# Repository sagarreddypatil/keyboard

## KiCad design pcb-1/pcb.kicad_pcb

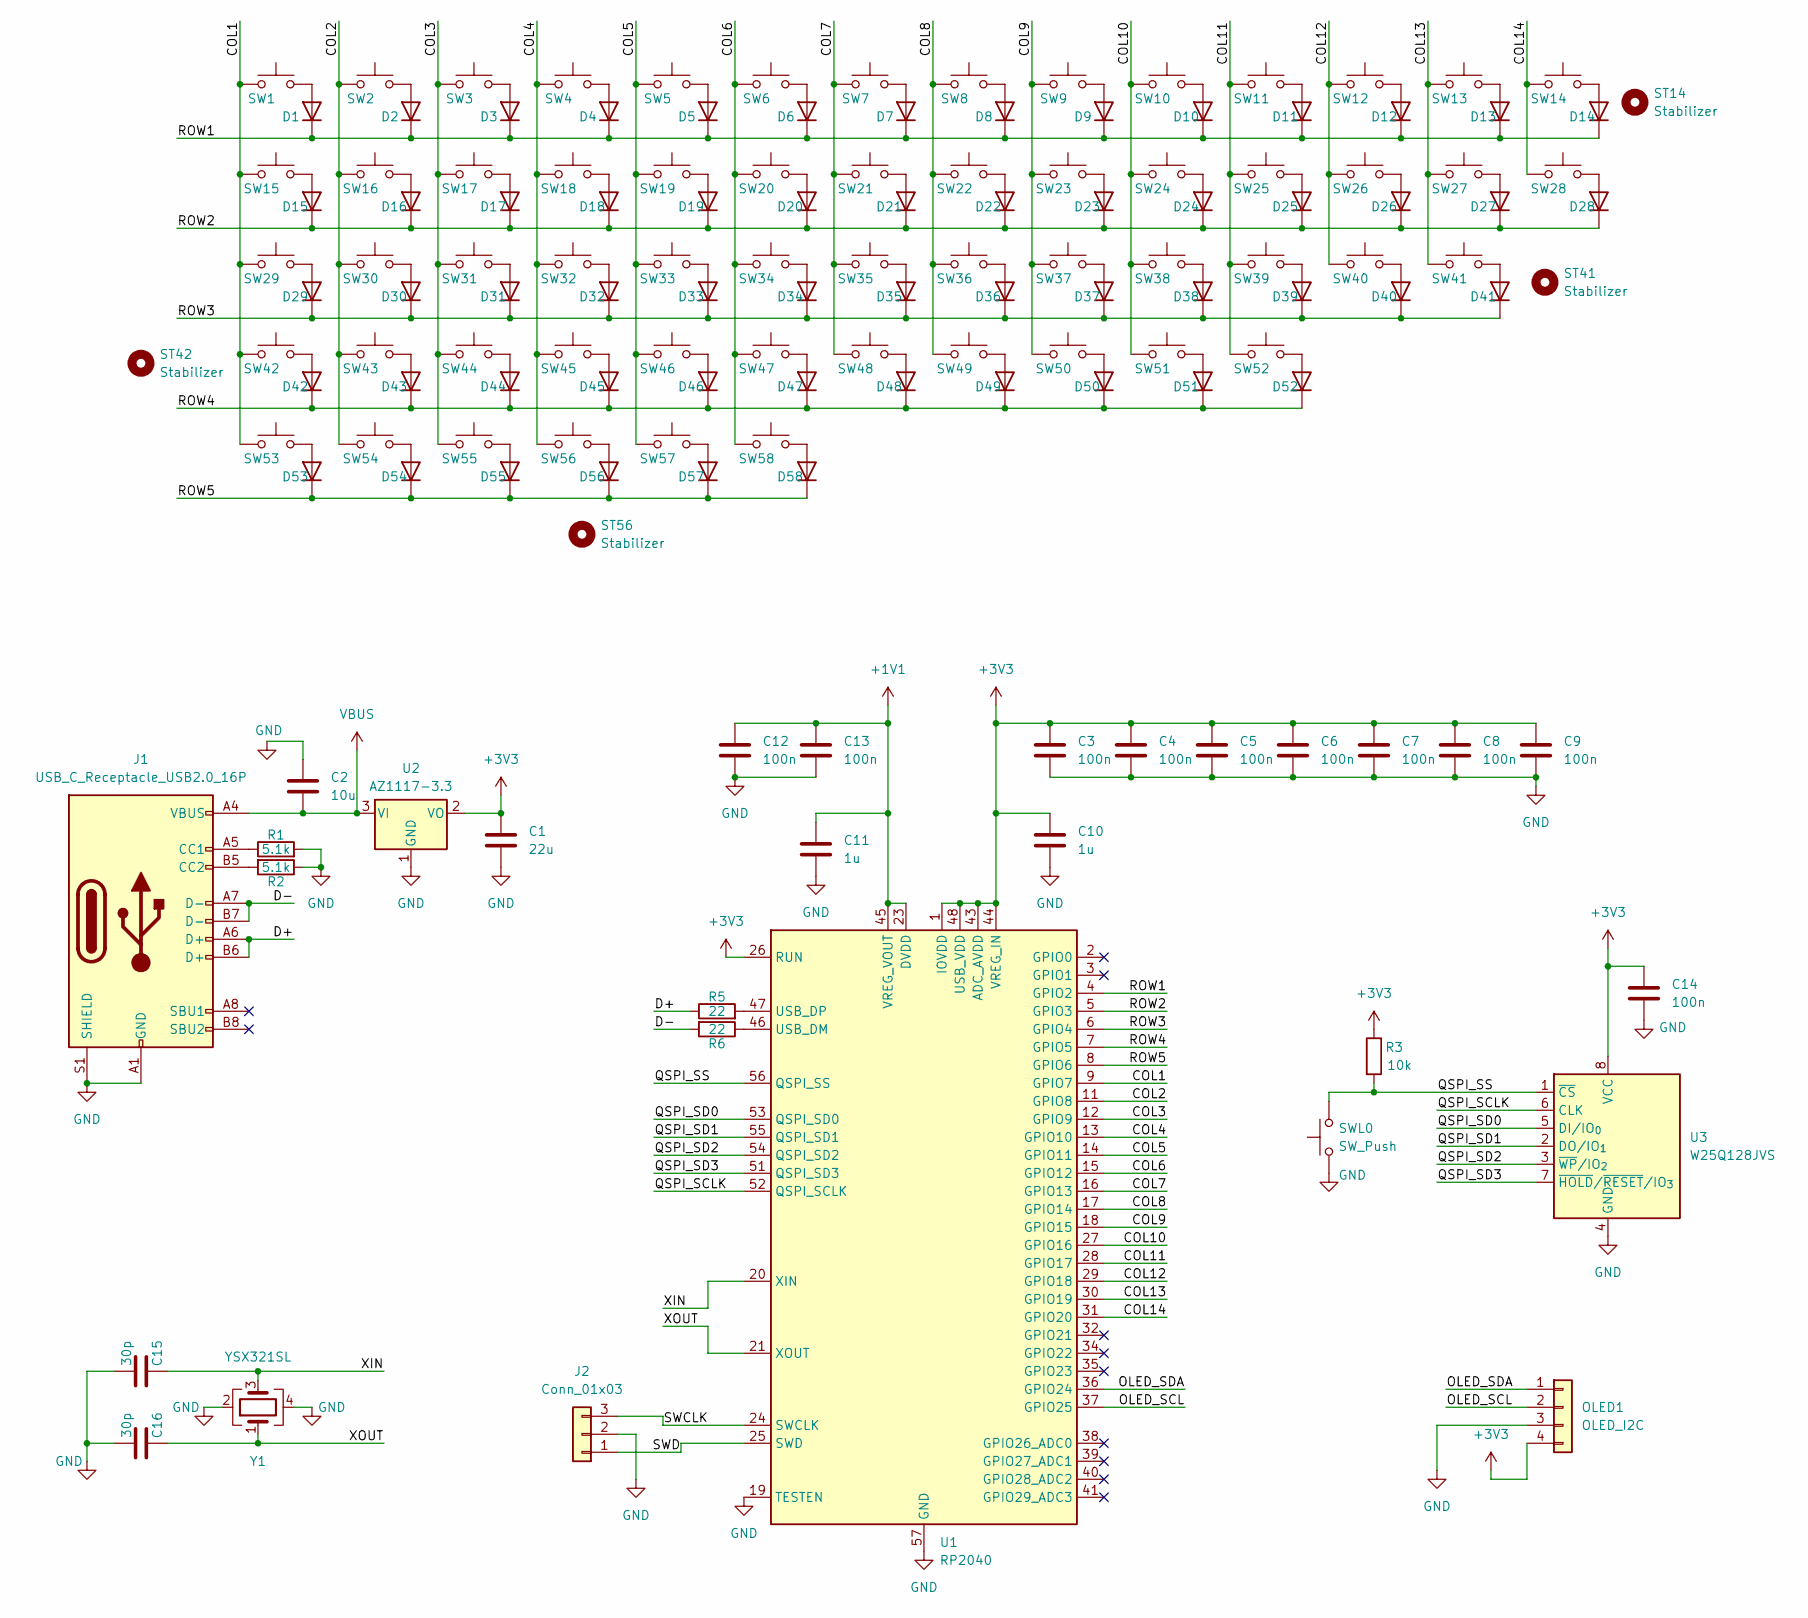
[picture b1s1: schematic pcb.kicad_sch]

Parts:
C1: 22u; C_0603_1608Metric; LCSC C59461
C2: 10u; C_0603_1608Metric; LCSC C19702
C3, C4, C5, C6, C7, C8, C9, C12, C13, C14: 100n; C_0402_1005Metric; LCSC C1525
C10, C11: 1u; C_0402_1005Metric; LCSC C52923
C15, C16: 30p; C_0603_1608Metric; LCSC C1658
D1, D2, D3, D4, D5, D6, D7, D8, D9, D10, D11, D12, D13, D14, D15, D16, D17, D18, D19, D20, D21, D22, D23, D24, D25, D26, D27, D28, D29, D30, D31, D32, D33, D34, D35, D36, D37, D38, D39, D40, D41, D42, D43, D44, D45, D46, D47, D48, D49, D50, D51, D52, D53, D54, D55, D56, D57, D58: 1N4148WS; D_SOD-323
J1: USB_C_Receptacle_USB2.0_16P; USB_C_Receptacle_G-Switch_GT-USB-7010ASV; LCSC C2927037
J2: Conn_01x03; PinHeader_1x03_P2.54mm_Vertical
OLED1: OLED_I2C; PinHeader_1x04_P2.54mm_Vertical
R1, R2: 5.1k; R_0402_1005Metric; LCSC C25905
R3: 10k; R_0402_1005Metric; LCSC C25744
R5, R6: 22; R_0402_1005Metric; LCSC C25092
ST14, ST41, ST42: Stabilizer; Stabilizer_Cherry_MX_2.00u
ST56: Stabilizer; Stabilizer_Cherry_MX_6.25u
SW1, SW2, SW3, SW4, SW5, SW6, SW7, SW8, SW9, SW10, SW11, SW12, SW13, SW16, SW17, SW18, SW19, SW20, SW21, SW22, SW23, SW24, SW25, SW26, SW27, SW30, SW31, SW32, SW33, SW34, SW35, SW36, SW37, SW38, SW39, SW40, SW43, SW44, SW45, SW46, SW47, SW48, SW49, SW50, SW51, SW52, SW58: SW_Push; SW_Cherry_MX_PCB_1.00u
SW14: SW_Push; SW_Cherry_MX_PCB_2.00u
SW15, SW28: SW_Push; SW_Cherry_MX_PCB_1.50u
SW29: SW_Push; SW_Cherry_MX_PCB_1.75u
SW41, SW42: SW_Push; SW_Cherry_MX_PCB_2.25u
SW53, SW54, SW55, SW57: SW_Push; SW_Cherry_MX_PCB_1.25u
SW56: SW_Push; SW_Cherry_MX_PCB_6.25u
SWL0: SW_Push; SW_Push_1P1T_XKB_TS-1187A; LCSC C318884
U1: RP2040; QFN-56-1EP_7x7mm_P0.4mm_EP3.2x3.2mm; LCSC C2040
U2: AZ1117-3.3; SOT-223-3_TabPin2; LCSC C6186
U3: W25Q128JVS; SOIC-8_5.3x5.3mm_P1.27mm; LCSC C97521
Y1: YSX321SL; Crystal_SMD_3225-4Pin_3.2x2.5mm; LCSC C9002

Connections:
+1V1: C11.1, C12.1, C13.1, U1.23 (DVDD), U1.45 (VREG_VOUT), U1.50 (DVDD)
+3V3: C1.1, C3.1, C4.1, C5.1, C6.1, C7.1, C8.1, C9.1, C10.1, C14.1, OLED1.4 (VCC), R3.1, U1.1 (IOVDD), U1.10 (IOVDD), U1.22 (IOVDD), U1.26 (RUN), U1.33 (IOVDD), U1.42 (IOVDD), U1.43 (ADC_AVDD), U1.44 (VREG_IN), U1.48 (USB_VDD), U1.49 (IOVDD), U2.2 (VO), U3.8 (VCC)
/COL1: SW1.1, SW15.1, SW29.1, SW42.1, SW53.1, U1.9 (GPIO7)
/COL2: SW2.1, SW16.1, SW30.1, SW43.1, SW54.1, U1.11 (GPIO8)
/COL3: SW3.1, SW17.1, SW31.1, SW44.1, SW55.1, U1.12 (GPIO9)
/COL4: SW4.1, SW18.1, SW32.1, SW45.1, SW56.1, U1.13 (GPIO10)
/COL5: SW5.1, SW19.1, SW33.1, SW46.1, SW57.1, U1.14 (GPIO11)
/COL6: SW6.1, SW20.1, SW34.1, SW47.1, SW58.1, U1.15 (GPIO12)
/COL7: SW7.1, SW21.1, SW35.1, SW48.1, U1.16 (GPIO13)
/COL8: SW8.1, SW22.1, SW36.1, SW49.1, U1.17 (GPIO14)
/COL9: SW9.1, SW23.1, SW37.1, SW50.1, U1.18 (GPIO15)
/COL10: SW10.1, SW24.1, SW38.1, SW51.1, U1.27 (GPIO16)
/COL11: SW11.1, SW25.1, SW39.1, SW52.1, U1.28 (GPIO17)
/COL12: SW12.1, SW26.1, SW40.1, U1.29 (GPIO18)
/COL13: SW13.1, SW27.1, SW41.1, U1.30 (GPIO19)
/COL14: SW14.1, SW28.1, U1.31 (GPIO20)
/D+: J1.A6 (D+), J1.B6 (D+), R5.1
/D-: J1.A7 (D-), J1.B7 (D-), R6.2
/OLED_SCL: OLED1.2 (SCL), U1.37 (GPIO25)
/OLED_SDA: OLED1.1 (SDA), U1.36 (GPIO24)
/QSPI_SCLK: U1.52 (QSPI_SCLK), U3.6 (CLK)
/QSPI_SD0: U1.53 (QSPI_SD0), U3.5 (DI/IO_{0})
/QSPI_SD1: U1.55 (QSPI_SD1), U3.2 (DO/IO_{1})
/QSPI_SD2: U1.54 (QSPI_SD2), U3.3 (~WP/IO_{2})
/QSPI_SD3: U1.51 (QSPI_SD3), U3.7 (~HOLD/~RESET/IO_{3})
/QSPI_SS: R3.2, SWL0.2, U1.56 (QSPI_SS), U3.1 (~CS)
/ROW1: D1.1 (K), D2.1 (K), D3.1 (K), D4.1 (K), D5.1 (K), D6.1 (K), D7.1 (K), D8.1 (K), D9.1 (K), D10.1 (K), D11.1 (K), D12.1 (K), D13.1 (K), D14.1 (K), U1.4 (GPIO2)
/ROW2: D15.1 (K), D16.1 (K), D17.1 (K), D18.1 (K), D19.1 (K), D20.1 (K), D21.1 (K), D22.1 (K), D23.1 (K), D24.1 (K), D25.1 (K), D26.1 (K), D27.1 (K), D28.1 (K), U1.5 (GPIO3)
/ROW3: D29.1 (K), D30.1 (K), D31.1 (K), D32.1 (K), D33.1 (K), D34.1 (K), D35.1 (K), D36.1 (K), D37.1 (K), D38.1 (K), D39.1 (K), D40.1 (K), D41.1 (K), U1.6 (GPIO4)
/ROW4: D42.1 (K), D43.1 (K), D44.1 (K), D45.1 (K), D46.1 (K), D47.1 (K), D48.1 (K), D49.1 (K), D50.1 (K), D51.1 (K), D52.1 (K), U1.7 (GPIO5)
/ROW5: D53.1 (K), D54.1 (K), D55.1 (K), D56.1 (K), D57.1 (K), D58.1 (K), U1.8 (GPIO6)
/SWCLK: J2.3, U1.24 (SWCLK)
/SWD: J2.1, U1.25 (SWD)
/XIN: C15.2, U1.20 (XIN), Y1.3
/XOUT: C16.2, U1.21 (XOUT), Y1.1
GND: C1.2, C2.1, C3.2, C4.2, C5.2, C6.2, C7.2, C8.2, C9.2, C10.2, C11.2, C12.2, C13.2, C14.2, C15.1, C16.1, J1.A1 (GND), J1.A12 (GND), J1.B1 (GND), J1.B12 (GND), J1.S1 (SHIELD), J2.2, OLED1.3 (GND), R1.2, R2.1, SWL0.1, U1.19 (TESTEN), U1.57 (GND), U2.1 (GND), U3.4 (GND), Y1.2, Y1.4
unnamed: D1.2 (A), SW1.2
unnamed: D2.2 (A), SW2.2
unnamed: D3.2 (A), SW3.2
unnamed: D4.2 (A), SW4.2
unnamed: D5.2 (A), SW5.2
unnamed: D6.2 (A), SW6.2
unnamed: D7.2 (A), SW7.2
unnamed: D8.2 (A), SW8.2
unnamed: D9.2 (A), SW9.2
unnamed: D10.2 (A), SW10.2
unnamed: D11.2 (A), SW11.2
unnamed: D12.2 (A), SW12.2
unnamed: D13.2 (A), SW13.2
unnamed: D14.2 (A), SW14.2
unnamed: D15.2 (A), SW15.2
unnamed: D16.2 (A), SW16.2
unnamed: D17.2 (A), SW17.2
unnamed: D18.2 (A), SW18.2
unnamed: D19.2 (A), SW19.2
unnamed: D20.2 (A), SW20.2
unnamed: D21.2 (A), SW21.2
unnamed: D22.2 (A), SW22.2
unnamed: D23.2 (A), SW23.2
unnamed: D24.2 (A), SW24.2
unnamed: D25.2 (A), SW25.2
unnamed: D26.2 (A), SW26.2
unnamed: D27.2 (A), SW27.2
unnamed: D28.2 (A), SW28.2
unnamed: D29.2 (A), SW29.2
unnamed: D30.2 (A), SW30.2
unnamed: D31.2 (A), SW31.2
unnamed: D32.2 (A), SW32.2
unnamed: D33.2 (A), SW33.2
unnamed: D34.2 (A), SW34.2
unnamed: D35.2 (A), SW35.2
unnamed: D36.2 (A), SW36.2
unnamed: D37.2 (A), SW37.2
unnamed: D38.2 (A), SW38.2
unnamed: D39.2 (A), SW39.2
unnamed: D40.2 (A), SW40.2
unnamed: D41.2 (A), SW41.2
unnamed: D42.2 (A), SW42.2
unnamed: D43.2 (A), SW43.2
unnamed: D44.2 (A), SW44.2
unnamed: D45.2 (A), SW45.2
unnamed: D46.2 (A), SW46.2
unnamed: D47.2 (A), SW47.2
unnamed: D48.2 (A), SW48.2
unnamed: D49.2 (A), SW49.2
unnamed: D50.2 (A), SW50.2
unnamed: D51.2 (A), SW51.2
unnamed: D52.2 (A), SW52.2
unnamed: D53.2 (A), SW53.2
unnamed: D54.2 (A), SW54.2
unnamed: D55.2 (A), SW55.2
unnamed: D56.2 (A), SW56.2
unnamed: D57.2 (A), SW57.2
unnamed: D58.2 (A), SW58.2
unnamed: J1.A5 (CC1), R1.1
unnamed: J1.B5 (CC2), R2.2
unnamed: R6.1, U1.46 (USB_DM)
unnamed: R5.2, U1.47 (USB_DP)
VBUS: C2.2, J1.A4 (VBUS), J1.A9 (VBUS), J1.B4 (VBUS), J1.B9 (VBUS), U2.3 (VI)

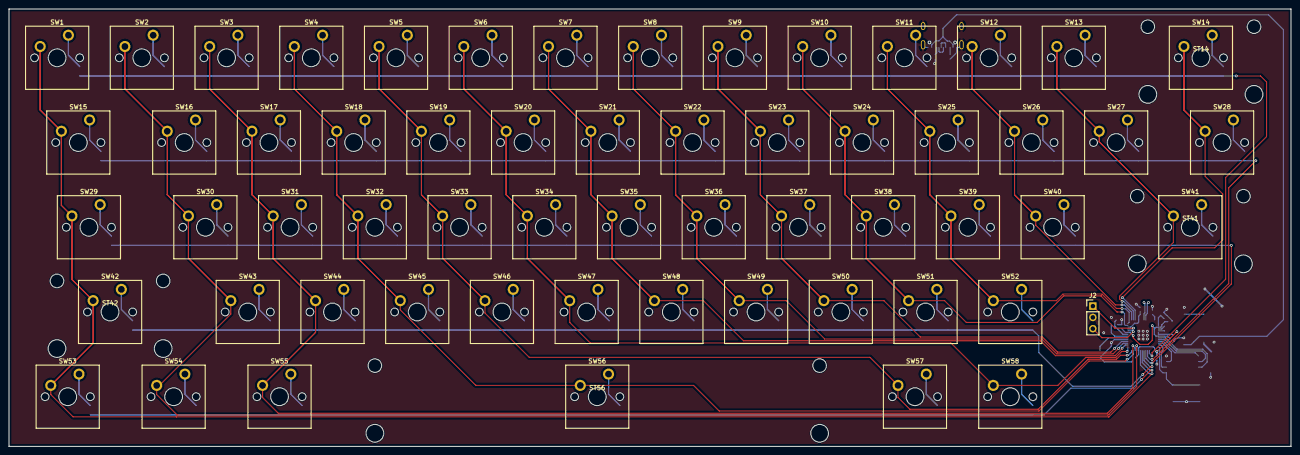
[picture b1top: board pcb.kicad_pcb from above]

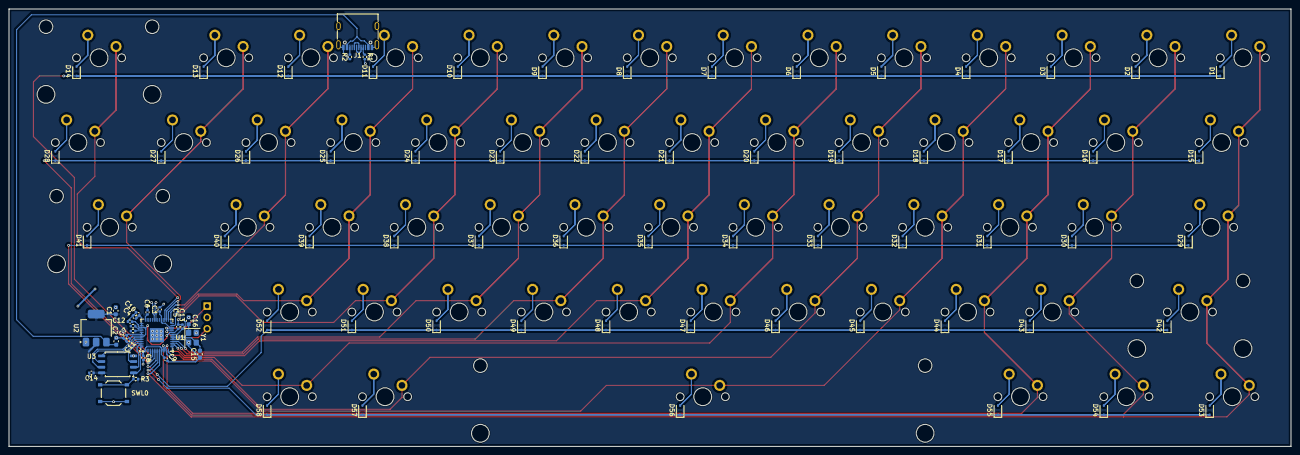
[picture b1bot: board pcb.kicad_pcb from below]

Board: 2 copper layers, 288.2 x 98.4 mm, 148 parts (85 on the bottom side), 97 nets.

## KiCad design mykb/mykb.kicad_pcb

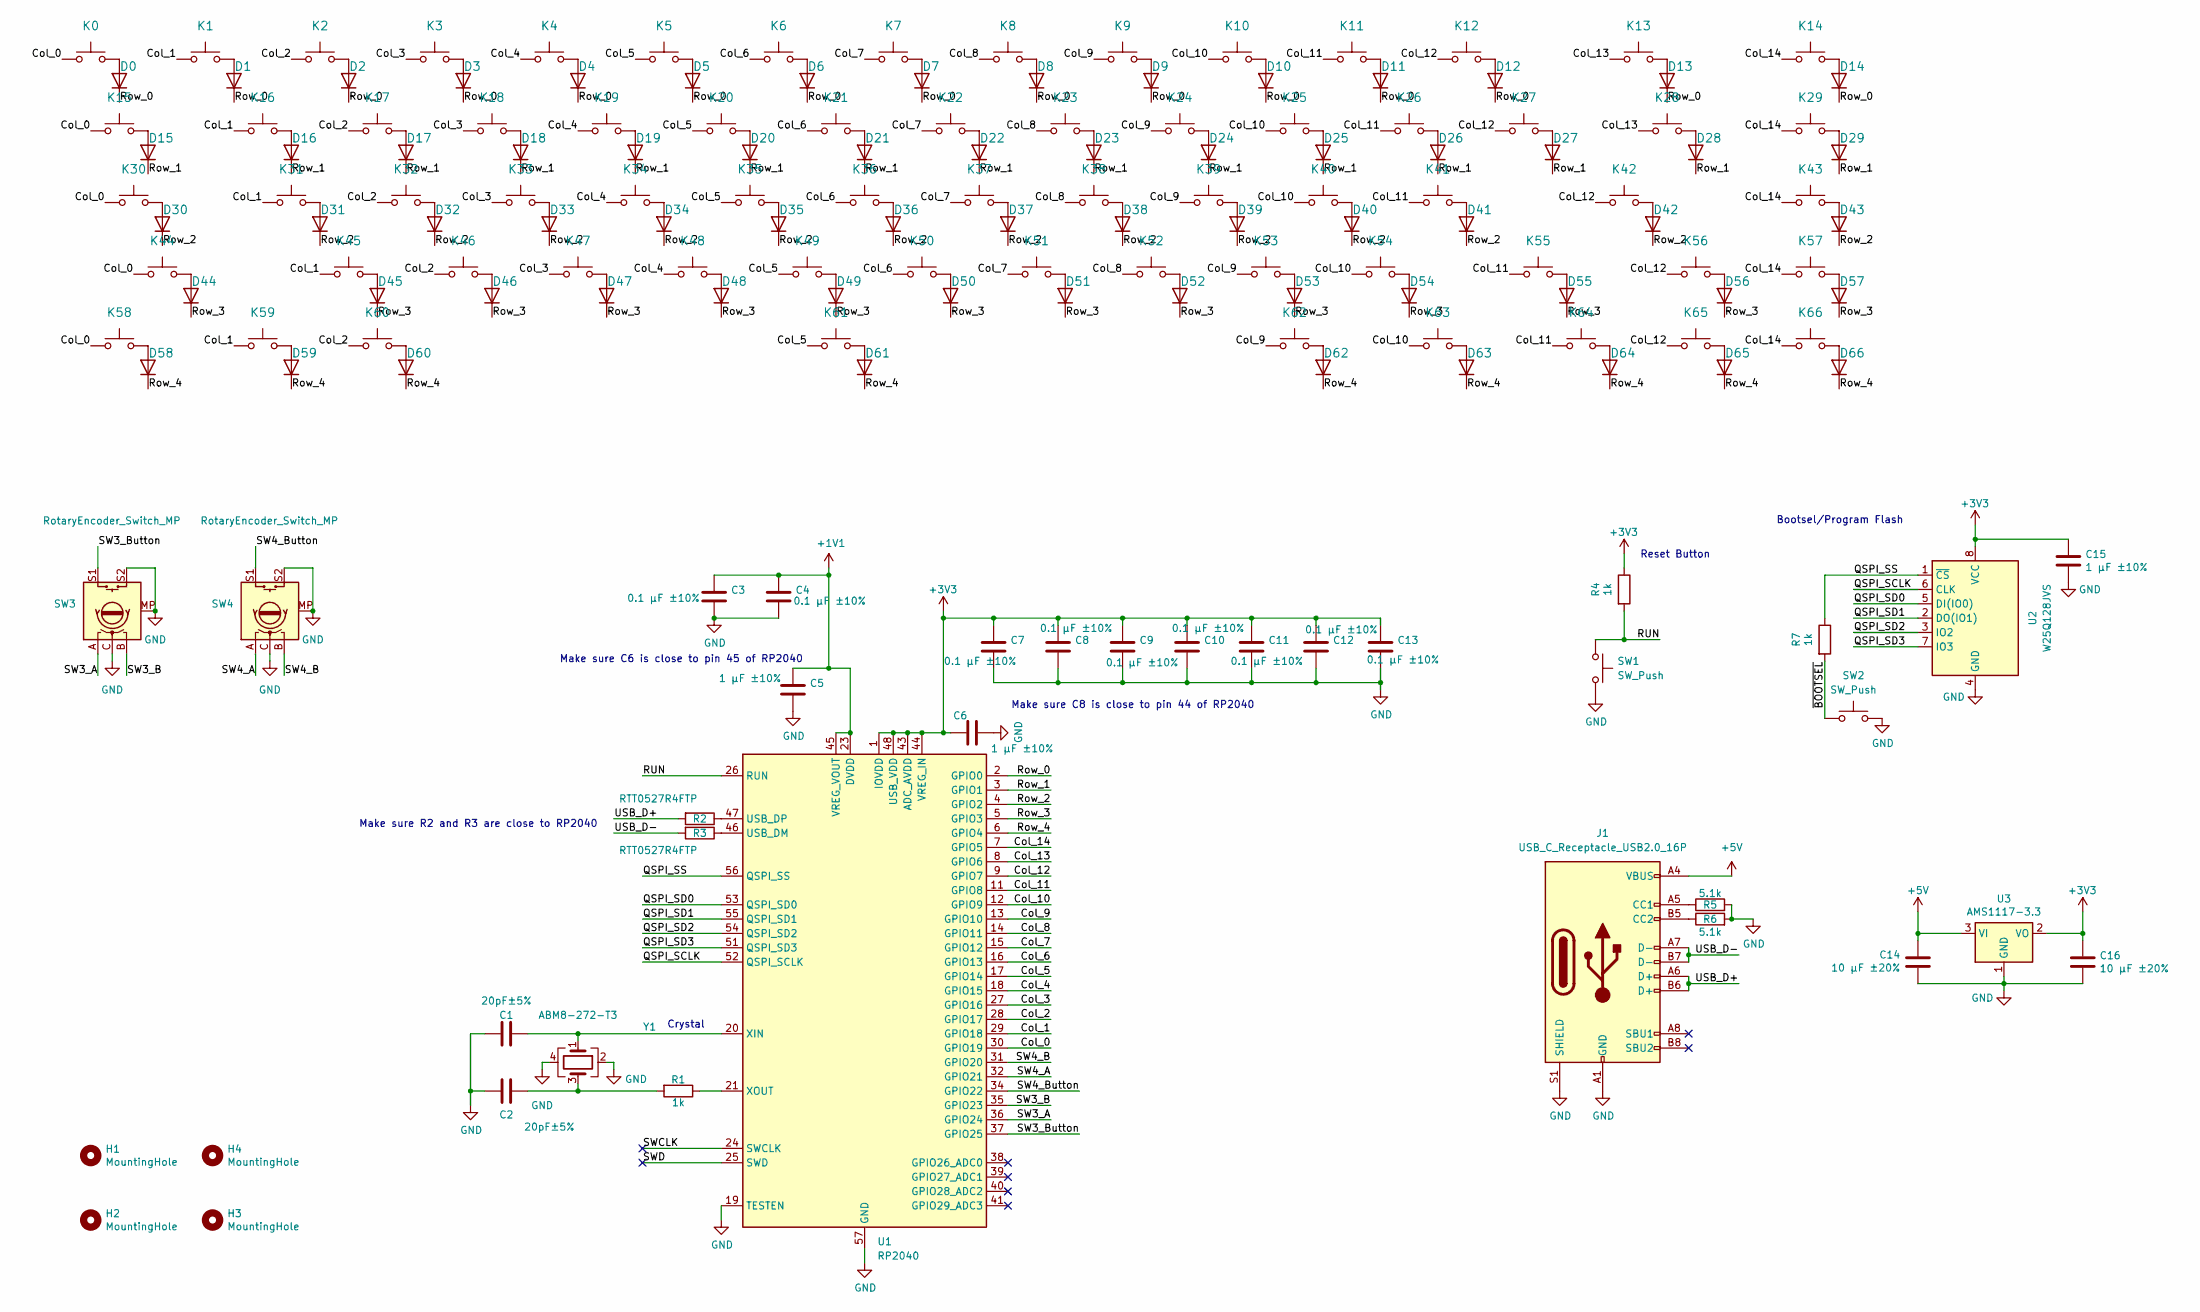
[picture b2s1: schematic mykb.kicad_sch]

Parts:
C1, C2: 20pF±5%; C_0402_1005Metric
C3, C4, C7, C8, C9, C10, C11, C12, C13: 0.1 µF ±10%; C_0402_1005Metric
C5, C6, C15: 1 µF ±10%; C_0402_1005Metric
C14, C16: 10 µF ±20%; C_0402_1005Metric
D0, D1, D2, D3, D4, D5, D6, D7, D8, D9, D10, D11, D12, D13, D14, D15, D16, D17, D18, D19, D20, D21, D22, D23, D24, D25, D26, D27, D28, D29, D30, D31, D32, D33, D34, D35, D36, D37, D38, D39, D40, D41, D42, D43, D44, D45, D46, D47, D48, D49, D50, D51, D52, D53, D54, D55, D56, D57, D58, D59, D60, D61, D62, D63, D64, D65, D66: 1N4148WS; D_SOD-323_HandSoldering
H1, H2, H3, H4: MountingHole; MountingHole_3.2mm_M3_DIN965
J1: USB_C_Receptacle_USB2.0_16P; USB_C_Receptacle_G-Switch_GT-USB-7010ASV
K0: Esc; SW_Cherry_MX_1.00u_PCB
K1: !,1; SW_Cherry_MX_1.00u_PCB
K2: @,2; SW_Cherry_MX_1.00u_PCB
K3: #,3; SW_Cherry_MX_1.00u_PCB
K4: $,4; SW_Cherry_MX_1.00u_PCB
K5: %,5; SW_Cherry_MX_1.00u_PCB
K6: ^,6; SW_Cherry_MX_1.00u_PCB
K7: &,7; SW_Cherry_MX_1.00u_PCB
K8: *,8; SW_Cherry_MX_1.00u_PCB
K9: (,9; SW_Cherry_MX_1.00u_PCB
K10: ),0; SW_Cherry_MX_1.00u_PCB
K11: _,-; SW_Cherry_MX_1.00u_PCB
K12: +,=; SW_Cherry_MX_1.00u_PCB
K13: Backspace; SW_Cherry_MX_2.00u_PCB
K14: Home; SW_Cherry_MX_1.00u_PCB
K15: Tab; SW_Cherry_MX_1.50u_PCB
K16: Q; SW_Cherry_MX_1.00u_PCB
K17: W; SW_Cherry_MX_1.00u_PCB
K18: E; SW_Cherry_MX_1.00u_PCB
K19: R; SW_Cherry_MX_1.00u_PCB
K20: T; SW_Cherry_MX_1.00u_PCB
K21: Y; SW_Cherry_MX_1.00u_PCB
K22: U; SW_Cherry_MX_1.00u_PCB
K23: I; SW_Cherry_MX_1.00u_PCB
K24: O; SW_Cherry_MX_1.00u_PCB
K25: P; SW_Cherry_MX_1.00u_PCB
K26: {,[; SW_Cherry_MX_1.00u_PCB
K27: },]; SW_Cherry_MX_1.00u_PCB
K28: |,\; SW_Cherry_MX_1.50u_PCB
K29: PgUp; SW_Cherry_MX_1.00u_PCB
K30: Caps Lock; SW_Cherry_MX_1.75u_PCB
K31: A; SW_Cherry_MX_1.00u_PCB
K32: S; SW_Cherry_MX_1.00u_PCB
K33, K47: KeyD; SW_Cherry_MX_1.00u_PCB
K34: F; SW_Cherry_MX_1.00u_PCB
K35: G; SW_Cherry_MX_1.00u_PCB
K36: H; SW_Cherry_MX_1.00u_PCB
K37: J; SW_Cherry_MX_1.00u_PCB
K38: K; SW_Cherry_MX_1.00u_PCB
K39: L; SW_Cherry_MX_1.00u_PCB
K40: :,;; SW_Cherry_MX_1.00u_PCB
K41: ",'; SW_Cherry_MX_1.00u_PCB
K42: Enter; SW_Cherry_MX_2.25u_PCB
K43: PgDn; SW_Cherry_MX_1.00u_PCB
K44: Shift; SW_Cherry_MX_2.25u_PCB
K45: Z; SW_Cherry_MX_1.00u_PCB
K46: X; SW_Cherry_MX_1.00u_PCB
K48: V; SW_Cherry_MX_1.00u_PCB
K49: B; SW_Cherry_MX_1.00u_PCB
K50: N; SW_Cherry_MX_1.00u_PCB
K51: M; SW_Cherry_MX_1.00u_PCB
K52: <,,; SW_Cherry_MX_1.00u_PCB
K53: >,.; SW_Cherry_MX_1.00u_PCB
K54: ?,/; SW_Cherry_MX_1.00u_PCB
K55: Shift; SW_Cherry_MX_1.75u_PCB
K56: ↑; SW_Cherry_MX_1.00u_PCB
K57: End; SW_Cherry_MX_1.00u_PCB
K58, K63: Ctrl; SW_Cherry_MX_1.50u_PCB
K59: Cmd; SW_Cherry_MX_1.00u_PCB
K60, K62: Alt; SW_Cherry_MX_1.00u_PCB
K61: Blank; SW_Cherry_MX_6.25u_PCB
K64: ←; SW_Cherry_MX_1.00u_PCB
K65: ↓; SW_Cherry_MX_1.00u_PCB
K66: →; SW_Cherry_MX_1.00u_PCB
R1, R4, R7: 1k; R_0402_1005Metric
R2, R3: RTT0527R4FTP; R_0805_2012Metric
R5, R6: 5.1k; R_0402_1005Metric
SW1, SW2: SW_Push; SW_PUSH_1P1T_6x3.5mm_H4.3_APEM_MJTP1243
SW3, SW4: RotaryEncoder_Switch_MP; RotaryEncoder_Alps_EC11E-Switch_Vertical_H20mm
U1: RP2040; QFN-56-1EP_7x7mm_P0.4mm_EP3.2x3.2mm
U2: W25Q128JVS; SOIC-8_5.23x5.23mm_P1.27mm
U3: AMS1117-3.3; SOT-223-3_TabPin2
Y1: ABM8-272-T3; ABM8272T3

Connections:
+1V1: C3.1, C4.1, C5.1, U1.23 (DVDD), U1.45 (VREG_VOUT), U1.50 (DVDD)
+3V3: C6.1, C7.1, C8.1, C9.1, C10.1, C11.1, C12.1, C13.1, C15.1, C16.1, R4.1, U1.1 (IOVDD), U1.10 (IOVDD), U1.22 (IOVDD), U1.33 (IOVDD), U1.42 (IOVDD), U1.43 (ADC_AVDD), U1.44 (VREG_IN), U1.48 (USB_VDD), U1.49 (IOVDD), U2.8 (VCC), U3.2 (VO)
+5V: C14.1, J1.A4 (VBUS), J1.A9 (VBUS), J1.B4 (VBUS), J1.B9 (VBUS), U3.3 (VI)
/Col_0: K0.1, K15.1, K30.1, K44.1, K58.1, U1.30 (GPIO19)
/Col_1: K1.1, K16.1, K31.1, K45.1, K59.1, U1.29 (GPIO18)
/Col_2: K2.1, K17.1, K32.1, K46.1, K60.1, U1.28 (GPIO17)
/Col_3: K3.1, K18.1, K33.1, K47.1, U1.27 (GPIO16)
/Col_4: K4.1, K19.1, K34.1, K48.1, U1.18 (GPIO15)
/Col_5: K5.1, K20.1, K35.1, K49.1, K61.1, U1.17 (GPIO14)
/Col_6: K6.1, K21.1, K36.1, K50.1, U1.16 (GPIO13)
/Col_7: K7.1, K22.1, K37.1, K51.1, U1.15 (GPIO12)
/Col_8: K8.1, K23.1, K38.1, K52.1, U1.14 (GPIO11)
/Col_9: K9.1, K24.1, K39.1, K53.1, K62.1, U1.13 (GPIO10)
/Col_10: K10.1, K25.1, K40.1, K54.1, K63.1, U1.12 (GPIO9)
/Col_11: K11.1, K26.1, K41.1, K55.1, K64.1, U1.11 (GPIO8)
/Col_12: K12.1, K27.1, K42.1, K56.1, K65.1, U1.9 (GPIO7)
/Col_13: K13.1, K28.1, U1.8 (GPIO6)
/Col_14: K14.1, K29.1, K43.1, K57.1, K66.1, U1.7 (GPIO5)
/QSPI_SCLK: U1.52 (QSPI_SCLK), U2.6 (CLK)
/QSPI_SD0: U1.53 (QSPI_SD0), U2.5 (DI(IO0))
/QSPI_SD1: U1.55 (QSPI_SD1), U2.2 (DO(IO1))
/QSPI_SD2: U1.54 (QSPI_SD2), U2.3 (IO2)
/QSPI_SD3: U1.51 (QSPI_SD3), U2.7 (IO3)
/QSPI_SS: R7.1, U1.56 (QSPI_SS), U2.1 (~CS)
/RUN: R4.2, SW1.1, U1.26 (RUN)
/Row_0: D0.1 (K), D1.1 (K), D2.1 (K), D3.1 (K), D4.1 (K), D5.1 (K), D6.1 (K), D7.1 (K), D8.1 (K), D9.1 (K), D10.1 (K), D11.1 (K), D12.1 (K), D13.1 (K), D14.1 (K), U1.2 (GPIO0)
/Row_1: D15.1 (K), D16.1 (K), D17.1 (K), D18.1 (K), D19.1 (K), D20.1 (K), D21.1 (K), D22.1 (K), D23.1 (K), D24.1 (K), D25.1 (K), D26.1 (K), D27.1 (K), D28.1 (K), D29.1 (K), U1.3 (GPIO1)
/Row_2: D30.1 (K), D31.1 (K), D32.1 (K), D33.1 (K), D34.1 (K), D35.1 (K), D36.1 (K), D37.1 (K), D38.1 (K), D39.1 (K), D40.1 (K), D41.1 (K), D42.1 (K), D43.1 (K), U1.4 (GPIO2)
/Row_3: D44.1 (K), D45.1 (K), D46.1 (K), D47.1 (K), D48.1 (K), D49.1 (K), D50.1 (K), D51.1 (K), D52.1 (K), D53.1 (K), D54.1 (K), D55.1 (K), D56.1 (K), D57.1 (K), U1.5 (GPIO3)
/Row_4: D58.1 (K), D59.1 (K), D60.1 (K), D61.1 (K), D62.1 (K), D63.1 (K), D64.1 (K), D65.1 (K), D66.1 (K), U1.6 (GPIO4)
/SW3_A: SW3.A, U1.36 (GPIO24)
/SW3_B: SW3.B, U1.35 (GPIO23)
/SW3_Button: SW3.S1, U1.37 (GPIO25)
/SW4_A: SW4.A, U1.32 (GPIO21)
/SW4_B: SW4.B, U1.31 (GPIO20)
/SW4_Button: SW4.S1, U1.34 (GPIO22)
/SWCLK: U1.24 (SWCLK)
/SWD: U1.25 (SWD)
/USB_D+: J1.A6 (D+), J1.B6 (D+), R2.2
/USB_D-: J1.A7 (D-), J1.B7 (D-), R3.2
/~BOOTSEL: R7.2, SW2.1
GND: C1.2, C2.2, C3.2, C4.2, C5.2, C6.2, C7.2, C8.2, C9.2, C10.2, C11.2, C12.2, C13.2, C14.2, C15.2, C16.2, J1.A1 (GND), J1.A12 (GND), J1.B1 (GND), J1.B12 (GND), J1.S1 (SHIELD), R5.2, R6.2, SW1.2, SW2.2, SW3.C, SW3.MP, SW3.S2, SW4.C, SW4.MP, SW4.S2, U1.19 (TESTEN), U1.57 (GND), U2.4 (GND), U3.1 (GND), Y1.2, Y1.4
unnamed: C2.1, R1.2, Y1.3
unnamed: D0.2 (A), K0.2
unnamed: D1.2 (A), K1.2
unnamed: D2.2 (A), K2.2
unnamed: D3.2 (A), K3.2
unnamed: D4.2 (A), K4.2
unnamed: D5.2 (A), K5.2
unnamed: D6.2 (A), K6.2
unnamed: D7.2 (A), K7.2
unnamed: D8.2 (A), K8.2
unnamed: D9.2 (A), K9.2
unnamed: D10.2 (A), K10.2
unnamed: D11.2 (A), K11.2
unnamed: D12.2 (A), K12.2
unnamed: D13.2 (A), K13.2
unnamed: D14.2 (A), K14.2
unnamed: D15.2 (A), K15.2
unnamed: D16.2 (A), K16.2
unnamed: D17.2 (A), K17.2
unnamed: D18.2 (A), K18.2
unnamed: D19.2 (A), K19.2
unnamed: D20.2 (A), K20.2
unnamed: D21.2 (A), K21.2
unnamed: D22.2 (A), K22.2
unnamed: D23.2 (A), K23.2
unnamed: D24.2 (A), K24.2
unnamed: D25.2 (A), K25.2
unnamed: D26.2 (A), K26.2
unnamed: D27.2 (A), K27.2
unnamed: D28.2 (A), K28.2
unnamed: D29.2 (A), K29.2
unnamed: D30.2 (A), K30.2
unnamed: D31.2 (A), K31.2
unnamed: D32.2 (A), K32.2
unnamed: D33.2 (A), K33.2
unnamed: D34.2 (A), K34.2
unnamed: D35.2 (A), K35.2
unnamed: D36.2 (A), K36.2
unnamed: D37.2 (A), K37.2
unnamed: D38.2 (A), K38.2
unnamed: D39.2 (A), K39.2
unnamed: D40.2 (A), K40.2
unnamed: D41.2 (A), K41.2
unnamed: D42.2 (A), K42.2
unnamed: D43.2 (A), K43.2
unnamed: D44.2 (A), K44.2
unnamed: D45.2 (A), K45.2
unnamed: D46.2 (A), K46.2
unnamed: D47.2 (A), K47.2
unnamed: D48.2 (A), K48.2
unnamed: D49.2 (A), K49.2
unnamed: D50.2 (A), K50.2
unnamed: D51.2 (A), K51.2
unnamed: D52.2 (A), K52.2
unnamed: D53.2 (A), K53.2
unnamed: D54.2 (A), K54.2
unnamed: D55.2 (A), K55.2
unnamed: D56.2 (A), K56.2
unnamed: D57.2 (A), K57.2
unnamed: D58.2 (A), K58.2
unnamed: D59.2 (A), K59.2
unnamed: D60.2 (A), K60.2
unnamed: D61.2 (A), K61.2
unnamed: D62.2 (A), K62.2
unnamed: D63.2 (A), K63.2
unnamed: D64.2 (A), K64.2
unnamed: D65.2 (A), K65.2
unnamed: D66.2 (A), K66.2
unnamed: J1.A5 (CC1), R5.1
unnamed: J1.B5 (CC2), R6.1
unnamed: R3.1, U1.46 (USB_DM)
unnamed: R2.1, U1.47 (USB_DP)
unnamed: C1.1, U1.20 (XIN), Y1.1
unnamed: R1.1, U1.21 (XOUT)

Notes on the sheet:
Crystal
Bootsel/Program Flash
Make sure C8 is close to pin 44 of RP2040
Reset Button
Make sure R2 and R3 are close to RP2040
Make sure C6 is close to pin 45 of RP2040

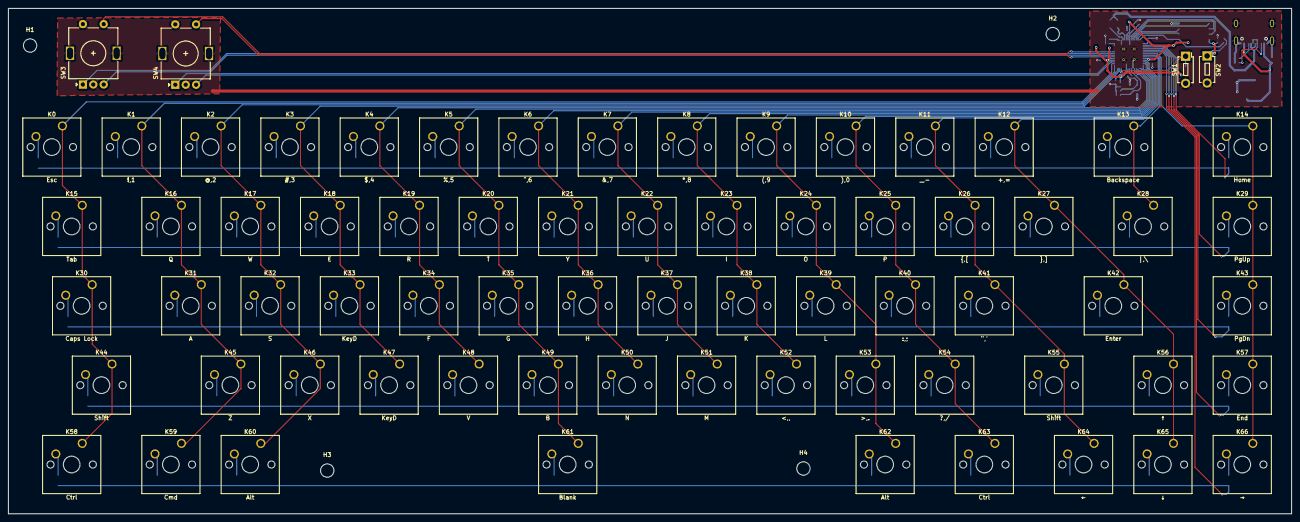
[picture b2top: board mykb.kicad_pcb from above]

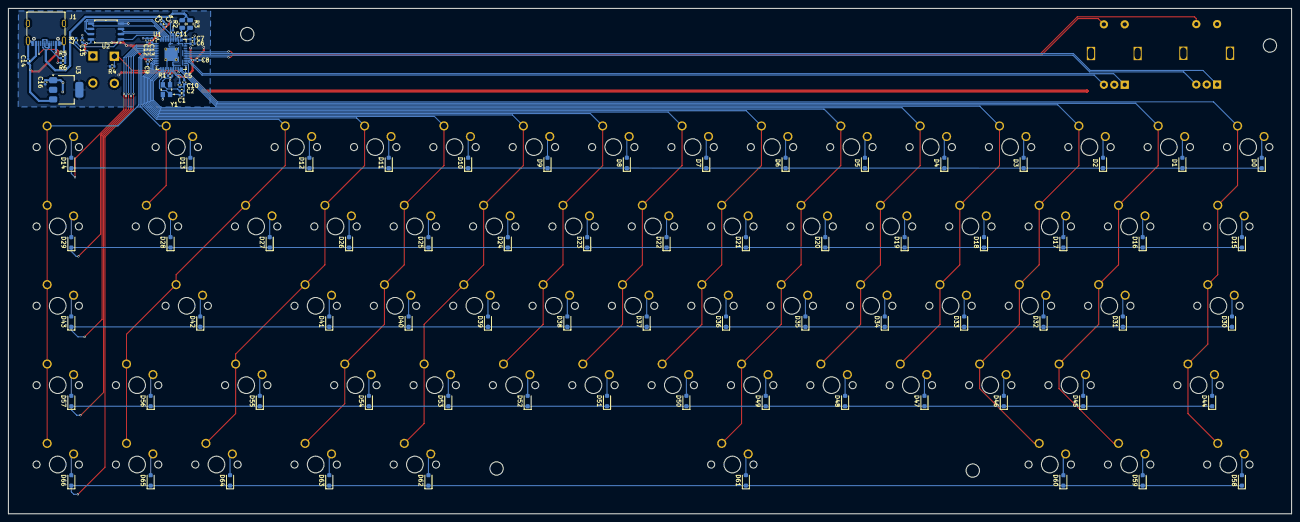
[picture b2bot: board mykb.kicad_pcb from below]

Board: 2 copper layers, 308.0 x 121.3 mm, 170 parts (95 on the bottom side), 114 nets.

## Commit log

2024-06-30 initial design
2024-07-03 trying again
2024-07-03 start new try
2024-07-06 progress on the redo
2024-07-06 github action?
2024-07-06 workdir
2024-07-06 bruh
2024-07-06 darn lockfiles
2024-07-06 firmware hello world
2024-07-08 more random ahh changes
2024-07-09 remove production files from repo
2024-07-23 stuff
2024-07-23 move part nums to description
2025-10-14 production version
2025-10-15 claude shit
2025-10-15 working
2025-10-15 rename external
2025-10-16 add stabilizers
2025-10-17 cleanup
2025-10-17 caps lock fn
2025-10-17 usb mfgr
2025-10-17 no docker
2025-10-17 stdio working
2025-10-19 display working
2025-10-19 new pcb wip
2025-10-19 oled read + cheese prevention
2025-10-19 oled
2025-11-11 remove new design
2026-02-08 remove cheese
2026-02-08 key debounce
2026-02-11 fix idk
2026-02-11 sticky fn
2026-02-11 a bunch of changes
